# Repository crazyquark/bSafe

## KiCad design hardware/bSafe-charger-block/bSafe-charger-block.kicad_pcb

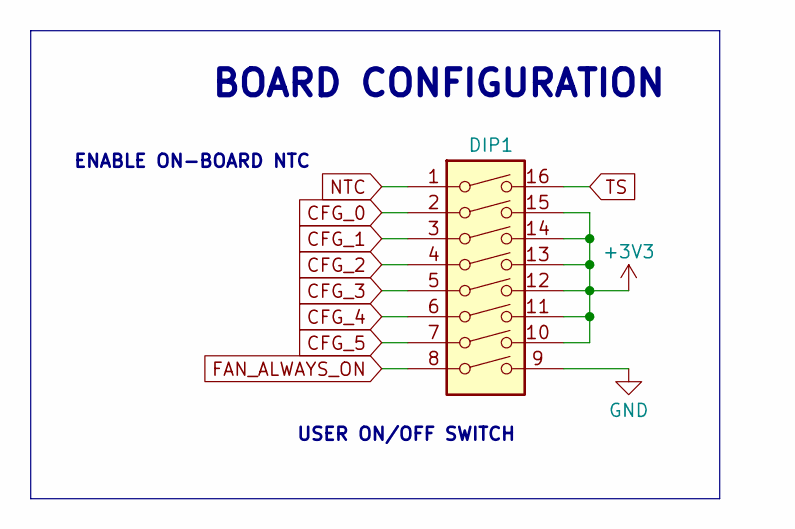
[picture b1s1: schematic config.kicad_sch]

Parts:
DIP1: SW_DIP_x08; SW_DIP_SPSTx08_Slide_Copal_CHS-08A_W5.08mm_P1.27mm_JPin

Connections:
+3V3: DIP1.10, DIP1.11, DIP1.12, DIP1.13, DIP1.14, DIP1.15; also elsewhere on the board
CFG_0: DIP1.2; also elsewhere on the board
CFG_1: DIP1.3; also elsewhere on the board
CFG_2: DIP1.4; also elsewhere on the board
CFG_3: DIP1.5; also elsewhere on the board
CFG_4: DIP1.6; also elsewhere on the board
CFG_5: DIP1.7; also elsewhere on the board
FAN_ALWAYS_ON: DIP1.8; also elsewhere on the board
GND: DIP1.9; also elsewhere on the board
NTC: DIP1.1; also elsewhere on the board
TS: DIP1.16; also elsewhere on the board

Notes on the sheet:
USER ON/OFF SWITCH
ENABLE ON-BOARD NTC
BOARD CONFIGURATION

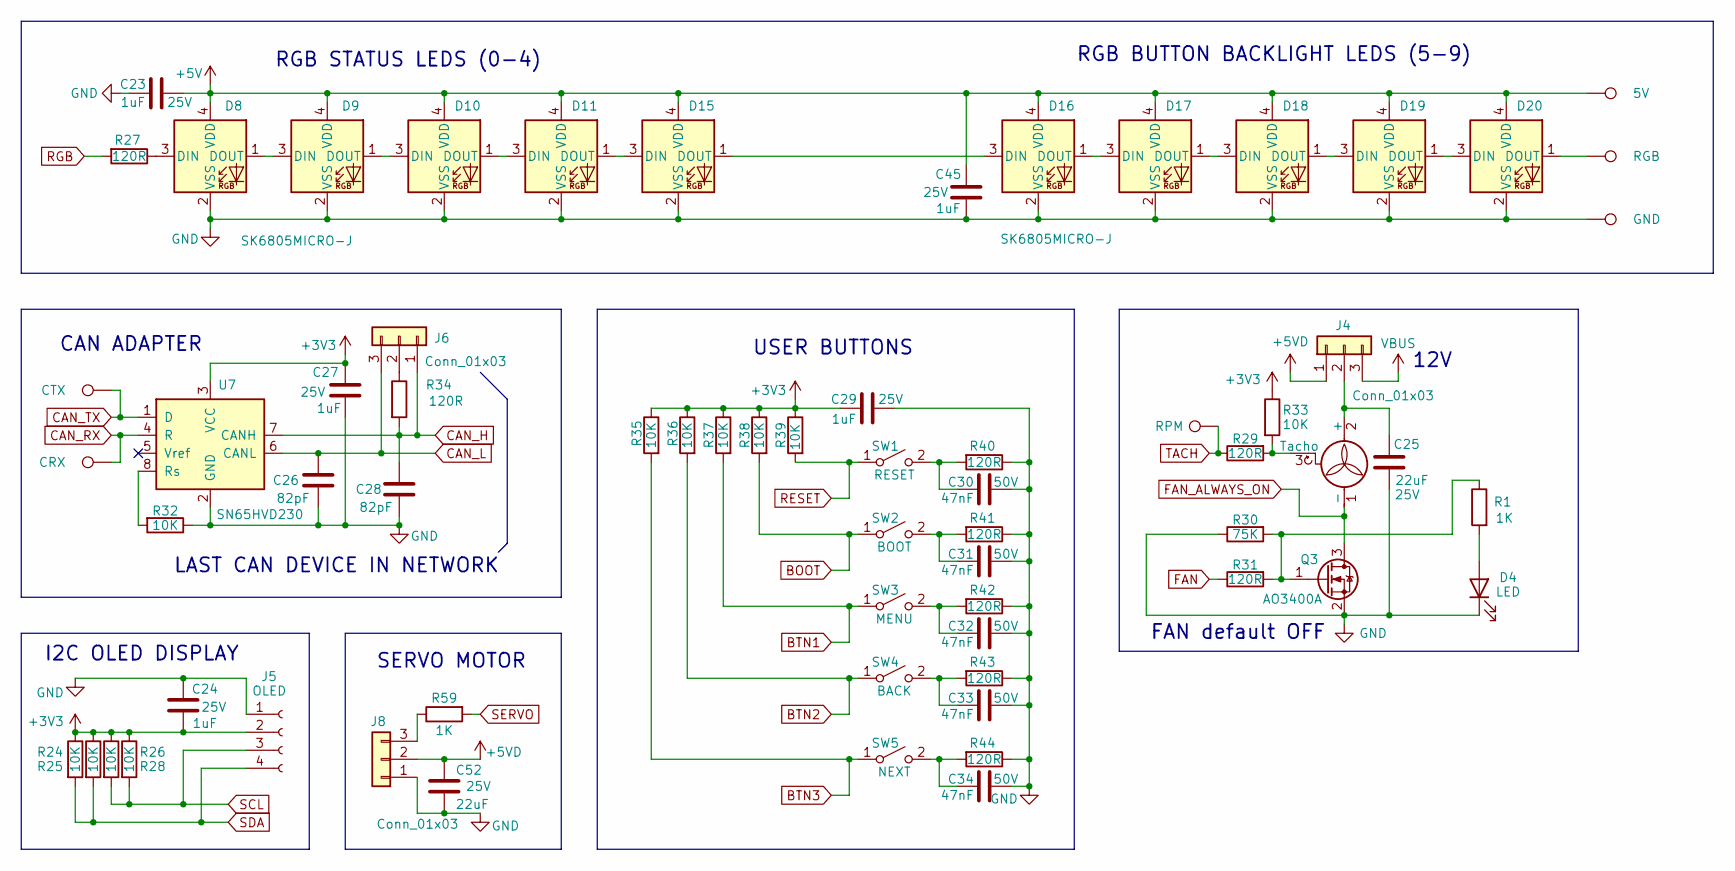
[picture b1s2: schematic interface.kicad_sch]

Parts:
C23, C24, C27, C29, C45: 1uF; C_0603_1608Metric; Voltage 25V
C25, C52: 22uF; C_0805_2012Metric; Voltage 25V
C26, C28: 82pF; C_0402_1005Metric
C30, C31, C32, C33, C34: 47nF; C_0402_1005Metric; Voltage 50V
D4: LED; LED_0402_1005Metric
D8, D9, D10, D11, D15, D16, D17, D18, D19, D20: SK6805MICRO-J; LED_SK6805_PLCC4_2.4x2.7mm_P1.3mm
J4, J6, J8: Conn_01x03; PinHeader_1x03_P2.54mm_Vertical
J5: OLED; Display_128x64_096_I2C
M1: Fan_3pin; Molex_KK-254_AE-6410-03A_1x03_P2.54mm_Vertical
Q3: AO3400A; SOT-23; JLCPCB C20917
R1, R59: 1K; R_0402_1005Metric
R24, R25, R26, R28, R32, R33, R35, R36, R37, R38, R39: 10K; R_0402_1005Metric
R27, R29, R31, R34, R40, R41, R42, R43, R44: 120R; R_0402_1005Metric
R30: 75K; R_0402_1005Metric
SW1: RESET; TS665WS
SW2: BOOT; TS665WS
SW3: MENU; TS665WS
SW4: BACK; TS665WS
SW5: NEXT; TS665WS
TP20: CTX; TestPoint_Pad_D1.5mm
TP21: CRX; TestPoint_Pad_D1.5mm
TP22: RPM; TestPoint_Pad_D1.5mm
TP25: 5V; TestPoint_Pad_D1.5mm
TP26: RGB; TestPoint_Pad_D1.5mm
TP27: GND; TestPoint_Pad_D1.5mm
U7: SN65HVD230; SOIC-8_3.9x4.9mm_P1.27mm

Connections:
+3V3: C24.2, C27.1, C29.2, J5.2, R24.1, R25.1, R26.1, R28.1, R33.1, R35.1, R36.1, R37.1, R38.1, R39.1, U7.3 (VCC); also elsewhere on the board
+5V: C23.1, C45.1, D8.4 (VDD), D9.4 (VDD), D10.4 (VDD), D11.4 (VDD), D15.4 (VDD), D16.4 (VDD), D17.4 (VDD), D18.4 (VDD), D19.4 (VDD), D20.4 (VDD), TP25.1; also elsewhere on the board
+5VD: C52.2, J4.1, J8.2; also elsewhere on the board
BOOT: R38.2, SW2.1 (A); also elsewhere on the board
BTN1: R37.2, SW3.1 (A); also elsewhere on the board
BTN2: R36.2, SW4.1 (A); also elsewhere on the board
BTN3: R35.2, SW5.1 (A); also elsewhere on the board
CAN_H: C28.1, J6.1, R34.2, U7.7 (CANH); also elsewhere on the board
CAN_L: C26.1, J6.3, U7.6 (CANL); also elsewhere on the board
CAN_RX: TP21.1, U7.4 (R); also elsewhere on the board
CAN_TX: TP20.1, U7.1 (D); also elsewhere on the board
FAN: R31.1; also elsewhere on the board
FAN_ALWAYS_ON: M1.1 (-), Q3.3 (D); also elsewhere on the board
GND: C23.2, C24.1, C25.2, C26.2, C27.2, C28.2, C29.1, C30.1, C31.1, C32.1, C33.1, C34.1, C45.2, C52.1, D4.1 (K), D8.2 (VSS), D9.2 (VSS), D10.2 (VSS), D11.2 (VSS), D15.2 (VSS), D16.2 (VSS), D17.2 (VSS), D18.2 (VSS), D19.2 (VSS), D20.2 (VSS), J5.1, J8.1, Q3.2 (S), R30.1, R32.1, R40.1, R41.1, R42.1, R43.1, R44.1, TP27.1, U7.2 (GND); also elsewhere on the board
unnamed: D4.2 (A), R1.2
unnamed: D8.3 (DIN), R27.1
unnamed: D8.1 (DOUT), D9.3 (DIN)
unnamed: D9.1 (DOUT), D10.3 (DIN)
unnamed: D10.1 (DOUT), D11.3 (DIN)
unnamed: D11.1 (DOUT), D15.3 (DIN)
unnamed: D15.1 (DOUT), D16.3 (DIN)
unnamed: D16.1 (DOUT), D17.3 (DIN)
unnamed: D17.1 (DOUT), D18.3 (DIN)
unnamed: D18.1 (DOUT), D19.3 (DIN)
unnamed: D19.1 (DOUT), D20.3 (DIN)
unnamed: D20.1 (DOUT), TP26.1
unnamed: C25.1, J4.2, M1.2 (+)
unnamed: J6.2, R34.1
unnamed: J8.3, R59.1
unnamed: M1.3 (Tacho), R29.2, R33.2
unnamed: Q3.1 (G), R1.1, R30.2, R31.2
unnamed: C30.2, R40.2, SW1.2 (B)
unnamed: C31.2, R41.2, SW2.2 (B)
unnamed: C32.2, R42.2, SW3.2 (B)
unnamed: C33.2, R43.2, SW4.2 (B)
unnamed: C34.2, R44.2, SW5.2 (B)
unnamed: R32.2, U7.8 (Rs)
RESET: R39.2, SW1.1 (A); also elsewhere on the board
RGB: R27.2; also elsewhere on the board
SCL: J5.3, R26.2, R28.2; also elsewhere on the board
SDA: J5.4, R24.2, R25.2; also elsewhere on the board
SERVO: R59.2; also elsewhere on the board
TACH: R29.1, TP22.1; also elsewhere on the board
VBUS: J4.3; also elsewhere on the board

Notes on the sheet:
I2C OLED DISPLAY
CAN ADAPTER
RGB STATUS LEDS (0-4)
SERVO MOTOR
RGB BUTTON BACKLIGHT LEDS (5-9)
FAN default OFF
12V
LAST CAN DEVICE IN NETWORK
USER BUTTONS

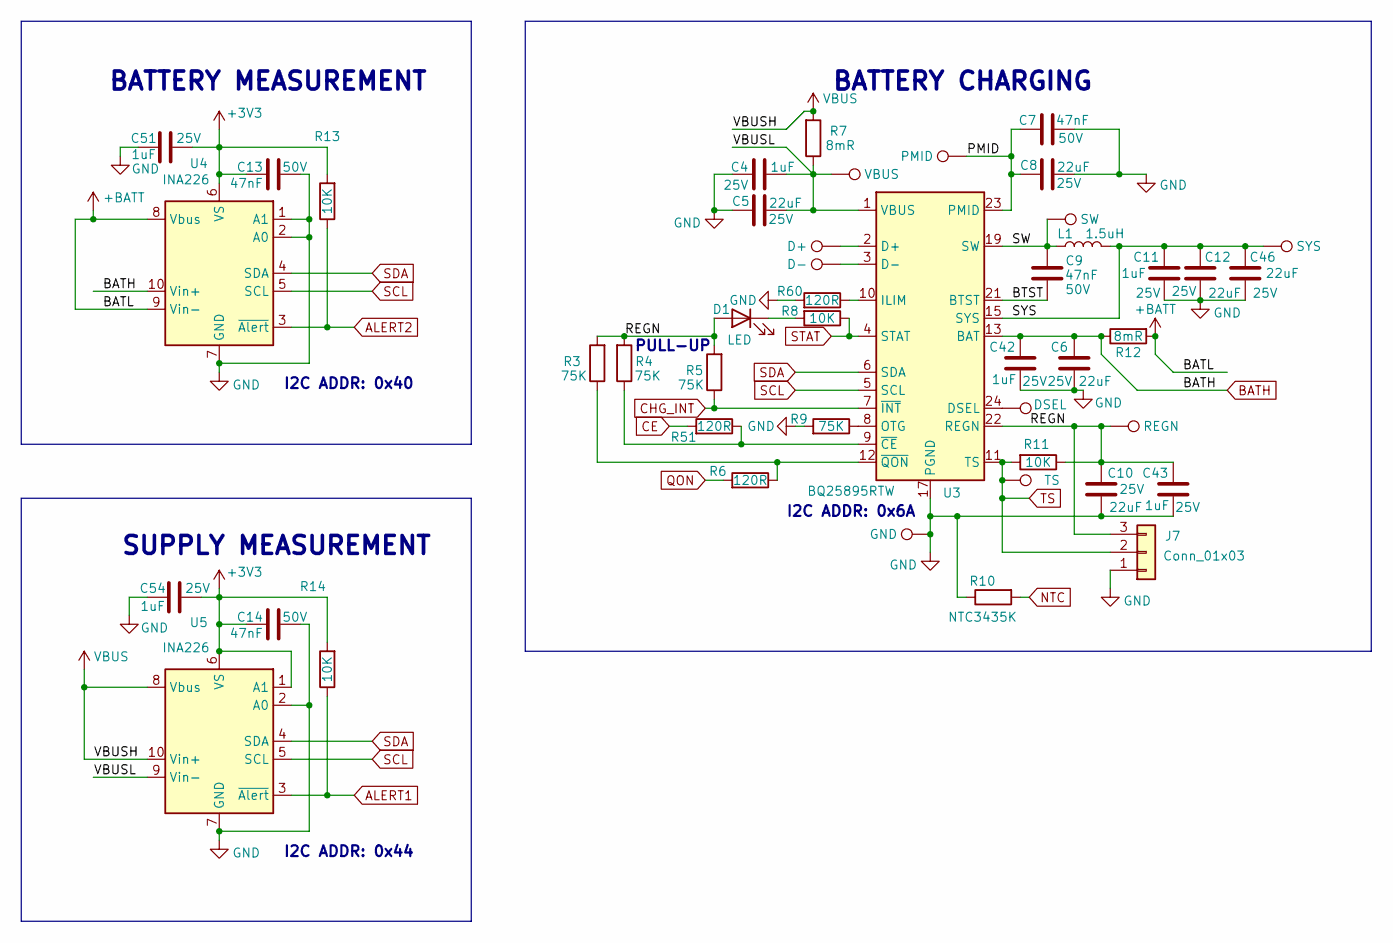
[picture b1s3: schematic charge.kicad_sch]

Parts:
C4, C11, C42, C43, C51, C54: 1uF; C_0603_1608Metric; Voltage 25V
C5, C6, C8, C10, C12, C46: 22uF; C_0805_2012Metric; Voltage 25V
C7, C9, C13, C14: 47nF; C_0402_1005Metric; Voltage 50V
D1: LED; LED_0402_1005Metric
J7: Conn_01x03; PinHeader_1x03_P2.54mm_Vertical
L1: 1.5uH; L_Sumida_CDMC6D28_7.25x6.5mm; JLCPCB C5189745
R3, R4, R5, R9: 75K; R_0402_1005Metric
R6, R51, R60: 120R; R_0402_1005Metric
R7, R12: 8mR; R_2512_6332Metric_Pad1.40x3.35mm_HandSolder
R8, R11, R13, R14: 10K; R_0402_1005Metric
R10: NTC3435K; R_0805_2012Metric_Pad1.20x1.40mm_HandSolder
TP3: DSEL; TestPoint_Pad_D1.5mm
TP4: SW; TestPoint_Pad_D1.5mm
TP7: VBUS; TestPoint_Pad_D1.5mm
TP9: PMID; TestPoint_Pad_D1.5mm
TP10: TS; TestPoint_Pad_D1.5mm
TP11: REGN; TestPoint_Pad_D1.5mm
TP13: SYS; TestPoint_Pad_D1.5mm
TP23: GND; TestPoint_Pad_D1.5mm
TP24: D+; TestPoint_Pad_D1.5mm
TP28: D-; TestPoint_Pad_D1.5mm
U3: BQ25895RTW; Texas_RTW_WQFN-24-1EP_4x4mm_P0.5mm_EP2.7x2.7mm_ThermalVias
U4, U5: INA226; VSSOP-10_3x3mm_P0.5mm

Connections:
+3V3: C13.2, C14.2, C51.1, C54.1, R13.2, R14.2, U4.6 (VS), U5.1 (A1), U5.6 (VS); also elsewhere on the board
+BATT: R12.2, U4.8 (Vbus), U4.9 (Vin-)
/charge/BTST: C9.1, U3.21 (BTST)
/charge/PMID: C7.2, C8.1, TP9.1, U3.23 (PMID)
/charge/REGN: C10.2, C43.2, D1.2 (A), J7.3, R3.2, R4.2, R5.2, R11.1, TP11.1, U3.22 (REGN)
/charge/SW: C9.2, L1.1, TP4.1, U3.19 (SW), U3.20 (SW)
/charge/SYS: C11.2, C12.1, C46.1, L1.2, TP13.1, U3.15 (SYS), U3.16 (SYS)
/charge/VBUSL: C4.1, C5.2, R7.1, TP7.1, U3.1 (VBUS), U5.9 (Vin-)
ALERT1: R14.1, U5.3 (~Alert); also elsewhere on the board
ALERT2: R13.1, U4.3 (~Alert); also elsewhere on the board
BATH: C6.1, C42.2, R12.1, U3.13 (BAT), U3.14 (BAT), U4.10 (Vin+); also elsewhere on the board
CE: R51.2; also elsewhere on the board
CHG_INT: R5.1, U3.7 (~INT); also elsewhere on the board
GND: C4.2, C5.1, C6.2, C7.1, C8.2, C10.1, C11.1, C12.2, C13.1, C14.1, C42.1, C43.1, C46.2, C51.2, C54.2, J7.1, R9.2, R10.1, R60.2, TP23.1, U3.17 (PGND), U3.18 (PGND), U3.25 (PGND), U4.1 (A1), U4.2 (A0), U4.7 (GND), U5.2 (A0), U5.7 (GND); also elsewhere on the board
NTC: R10.2; also elsewhere on the board
unnamed: D1.1 (K), R8.2
unnamed: TP24.1, U3.2 (D+)
unnamed: TP28.1, U3.3 (D-)
unnamed: TP3.1, U3.24 (DSEL)
unnamed: R60.1, U3.10 (ILIM)
unnamed: R9.1, U3.8 (OTG)
unnamed: R4.1, R51.1, U3.9 (~CE)
unnamed: R3.1, R6.1, U3.12 (~QON)
QON: R6.2; also elsewhere on the board
SCL: U3.5 (SCL), U4.5 (SCL), U5.5 (SCL); also elsewhere on the board
SDA: U3.6 (SDA), U4.4 (SDA), U5.4 (SDA); also elsewhere on the board
STAT: R8.1, U3.4 (STAT); also elsewhere on the board
TS: J7.2, R11.2, TP10.1, U3.11 (TS); also elsewhere on the board
VBUS: R7.2, U5.8 (Vbus), U5.10 (Vin+); also elsewhere on the board

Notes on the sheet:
SUPPLY MEASUREMENT
I2C ADDR: 0x44
I2C ADDR: 0x40
BATTERY CHARGING
I2C ADDR: 0x6A
PULL-UP
BATTERY MEASUREMENT

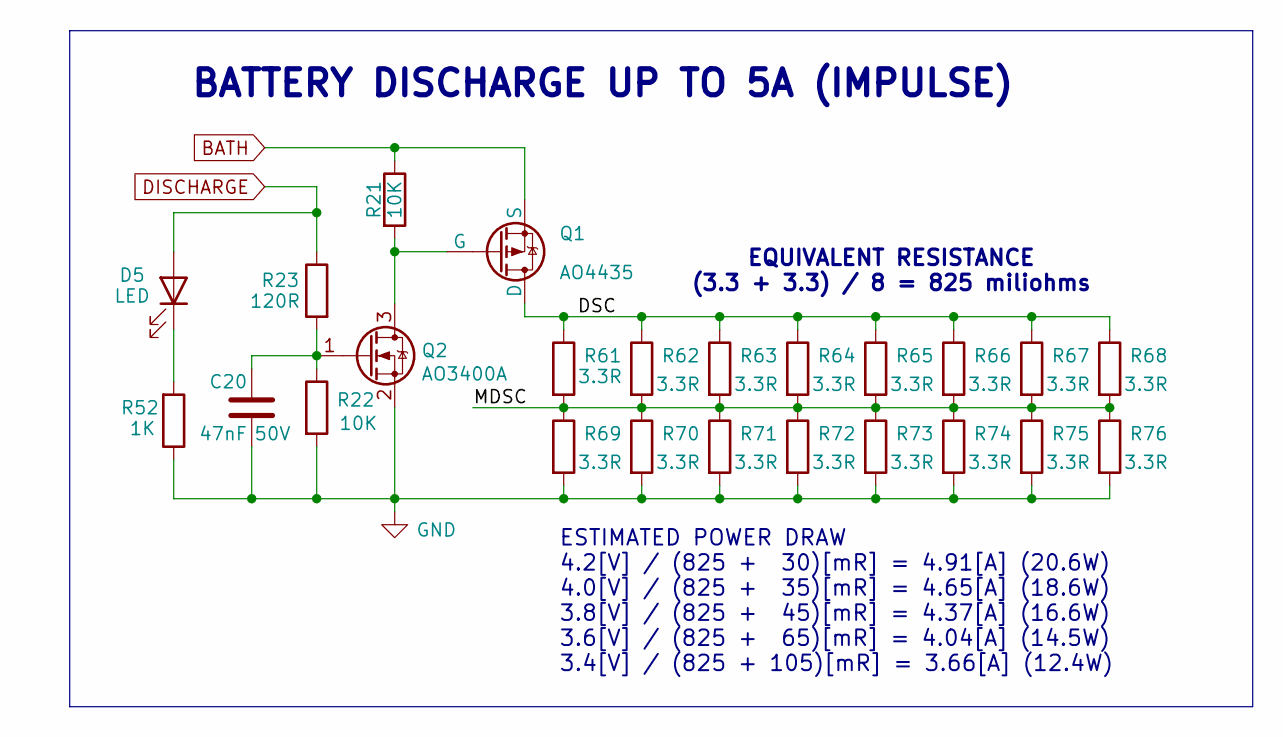
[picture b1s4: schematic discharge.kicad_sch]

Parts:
C20: 47nF; C_0402_1005Metric; Voltage 50V
D5: LED; LED_0402_1005Metric
Q1: AO4435; SOP-8_3.76x4.96mm_P1.27mm
Q2: AO3400A; SOT-23; JLCPCB C20917
R21, R22: 10K; R_0402_1005Metric
R23: 120R; R_0402_1005Metric
R52: 1K; R_0402_1005Metric
R61, R62, R63, R64, R65, R66, R67, R68, R69, R70, R71, R72, R73, R74, R75, R76: 3.3R; R_2512_6332Metric_Pad1.40x3.35mm_HandSolder

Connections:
/discharge/DSC: Q1.5 (D), Q1.6 (D), Q1.7 (D), Q1.8 (D), R61.1, R62.1, R63.1, R64.1, R65.1, R66.1, R67.1, R68.1
/discharge/MDSC: R61.2, R62.2, R63.2, R64.2, R65.2, R66.2, R67.2, R68.2, R69.1, R70.1, R71.1, R72.1, R73.1, R74.1, R75.1, R76.1
BATH: Q1.1 (S), Q1.2 (S), Q1.3 (S), R21.1; also elsewhere on the board
DISCHARGE: D5.2 (A), R23.1; also elsewhere on the board
GND: C20.2, Q2.2 (S), R22.2, R52.1, R69.2, R70.2, R71.2, R72.2, R73.2, R74.2, R75.2, R76.2; also elsewhere on the board
unnamed: D5.1 (K), R52.2
unnamed: Q1.4 (G), Q2.3 (D), R21.2
unnamed: C20.1, Q2.1 (G), R22.1, R23.2

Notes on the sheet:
EQUIVALENT RESISTANCE (3.3 + 3.3) / 8 = 825 miliohms
ESTIMATED POWER DRAW 4.2[V] / (825 + 30)[mR] = 4.91[A] (20.6W) 4.0[V] / (825 + 35)[mR] = 4.65[A] (18.6W) 3.8[V] / (825 + 45)[mR] = 4.37[A] (16.6W) 3.6[V] / (825 + 65)[mR] = 4.04[A] (14.5W) 3.4[V] / (825 + 105)[mR] = 3.66[A] (12.4W)
BATTERY DISCHARGE UP TO 5A (IMPULSE)

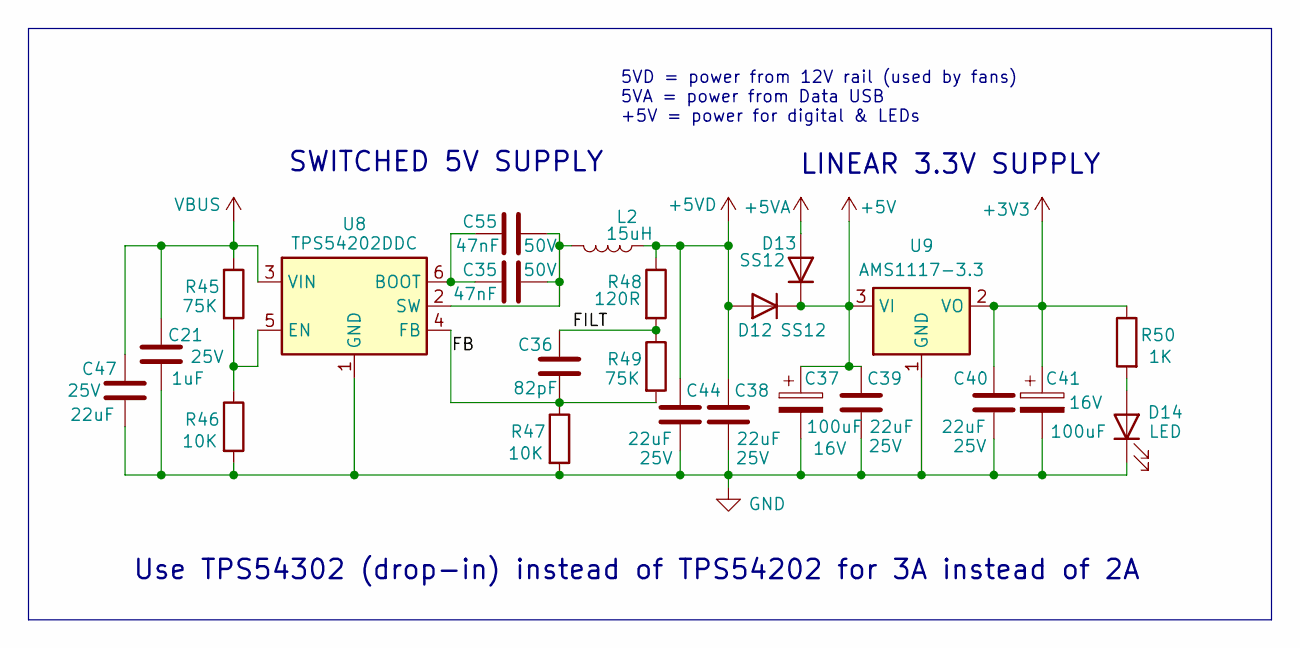
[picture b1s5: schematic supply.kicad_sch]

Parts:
C21: 1uF; C_0603_1608Metric; Voltage 25V
C35, C55: 47nF; C_0402_1005Metric; Voltage 50V
C36: 82pF; C_0402_1005Metric
C37, C41: 100uF; CP_Elec_6.3x5.4_Nichicon; Voltage 16V
C38, C39, C40, C44, C47: 22uF; C_0805_2012Metric; Voltage 25V
D12, D13: SS12; D_SMA
D14: LED; LED_0402_1005Metric
L2: 15uH; L_Taiyo-Yuden_NR-60xx
R45, R49: 75K; R_0402_1005Metric
R46, R47: 10K; R_0402_1005Metric
R48: 120R; R_0402_1005Metric
R50: 1K; R_0402_1005Metric
U8: TPS54202DDC; SOT-23-6
U9: AMS1117-3.3; SOT-223-3_TabPin2

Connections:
+3V3: C40.1, C41.1, R50.1, U9.2 (VO); also elsewhere on the board
+5V: C37.1, C39.1, D12.1 (K), D13.1 (K), U9.3 (VI); also elsewhere on the board
+5VA: D13.2 (A); also elsewhere on the board
+5VD: C38.1, C44.1, D12.2 (A), L2.2, R48.1; also elsewhere on the board
/supply/FB: C36.2, R47.1, R49.2, U8.4 (FB)
/supply/FILT: C36.1, R48.2, R49.1
GND: C21.2, C37.2, C38.2, C39.2, C40.2, C41.2, C44.2, C47.1, D14.1 (K), R46.2, R47.2, U8.1 (GND), U9.1 (GND); also elsewhere on the board
unnamed: D14.2 (A), R50.2
unnamed: C35.2, C55.2, U8.6 (BOOT)
unnamed: R45.2, R46.1, U8.5 (EN)
unnamed: C35.1, C55.1, L2.1, U8.2 (SW)
VBUS: C21.1, C47.2, R45.1, U8.3 (VIN); also elsewhere on the board

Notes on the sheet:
5VD = power from 12V rail (used by fans) 5VA = power from Data USB +5V = power for digital & LEDs
SWITCHED 5V SUPPLY
Use TPS54302 (drop-in) instead of TPS54202 for 3A instead of 2A
LINEAR 3.3V SUPPLY

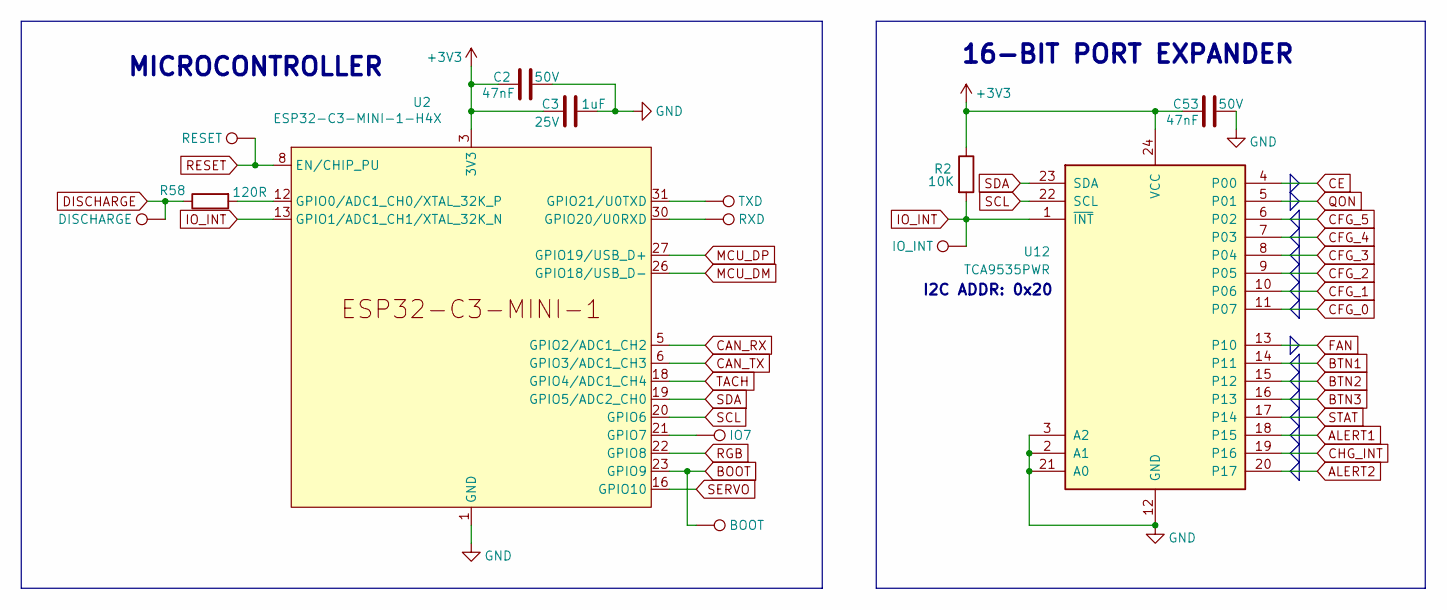
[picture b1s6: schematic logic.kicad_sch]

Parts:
C2, C53: 47nF; C_0402_1005Metric; Voltage 50V
C3: 1uF; C_0603_1608Metric; Voltage 25V
R2: 10K; R_0402_1005Metric
R58: 120R; R_0402_1005Metric
TP1: IO_INT; TestPoint_Pad_D1.5mm
TP2: IO7; TestPoint_Pad_D1.5mm
TP5: TXD; TestPoint_Pad_D1.5mm
TP6: RXD; TestPoint_Pad_D1.5mm
TP8: DISCHARGE; TestPoint_Pad_D1.5mm
TP30: RESET; TestPoint_Pad_D1.5mm
TP31: BOOT; TestPoint_Pad_D1.5mm
U2: ESP32-C3-MINI-1-H4X; ESP32-C3-MINI-1
U12: TCA9535PWR; TSSOP-24_4.4x7.8mm_P0.65mm

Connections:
+3V3: C2.2, C3.2, C53.2, R2.1, U2.3 (3V3), U12.24 (VCC); also elsewhere on the board
ALERT1: U12.18 (P15); also elsewhere on the board
ALERT2: U12.20 (P17); also elsewhere on the board
BOOT: TP31.1, U2.23 (GPIO9); also elsewhere on the board
BTN1: U12.14 (P11); also elsewhere on the board
BTN2: U12.15 (P12); also elsewhere on the board
BTN3: U12.16 (P13); also elsewhere on the board
CAN_RX: U2.5 (GPIO2/ADC1_CH2); also elsewhere on the board
CAN_TX: U2.6 (GPIO3/ADC1_CH3); also elsewhere on the board
CE: U12.4 (P00); also elsewhere on the board
CFG_0: U12.11 (P07); also elsewhere on the board
CFG_1: U12.10 (P06); also elsewhere on the board
CFG_2: U12.9 (P05); also elsewhere on the board
CFG_3: U12.8 (P04); also elsewhere on the board
CFG_4: U12.7 (P03); also elsewhere on the board
CFG_5: U12.6 (P02); also elsewhere on the board
CHG_INT: U12.19 (P16); also elsewhere on the board
DISCHARGE: R58.1, TP8.1; also elsewhere on the board
FAN: U12.13 (P10); also elsewhere on the board
GND: C2.1, C3.1, C53.1, U2.1 (GND), U2.2 (GND), U2.11 (GND), U2.14 (GND), U2.36 (GND), U2.37 (GND), U2.38 (GND), U2.39 (GND), U2.40 (GND), U2.41 (GND), U2.42 (GND), U2.43 (GND), U2.44 (GND), U2.45 (GND), U2.46 (GND), U2.47 (GND), U2.48 (GND), U2.49 (GND), U2.50 (GND), U2.51 (GND), U2.52 (GND), U2.53 (GND), U12.2 (A1), U12.3 (A2), U12.12 (GND), U12.21 (A0); also elsewhere on the board
IO_INT: R2.2, TP1.1, U2.13 (GPIO1/ADC1_CH1/XTAL_32K_N), U12.1 (~INT)
MCU_DM: U2.26 (GPIO18/USB_D-); also elsewhere on the board
MCU_DP: U2.27 (GPIO19/USB_D+); also elsewhere on the board
unnamed: R58.2, U2.12 (GPIO0/ADC1_CH0/XTAL_32K_P)
unnamed: TP2.1, U2.21 (GPIO7)
unnamed: TP6.1, U2.30 (GPIO20/U0RXD)
unnamed: TP5.1, U2.31 (GPIO21/U0TXD)
QON: U12.5 (P01); also elsewhere on the board
RESET: TP30.1, U2.8 (EN/CHIP_PU); also elsewhere on the board
RGB: U2.22 (GPIO8); also elsewhere on the board
SCL: U2.20 (GPIO6), U12.22 (SCL); also elsewhere on the board
SDA: U2.19 (GPIO5/ADC2_CH0), U12.23 (SDA); also elsewhere on the board
SERVO: U2.16 (GPIO10); also elsewhere on the board
STAT: U12.17 (P14); also elsewhere on the board
TACH: U2.18 (GPIO4/ADC1_CH4); also elsewhere on the board

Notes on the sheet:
MICROCONTROLLER
16-BIT PORT EXPANDER
I2C ADDR: 0x20

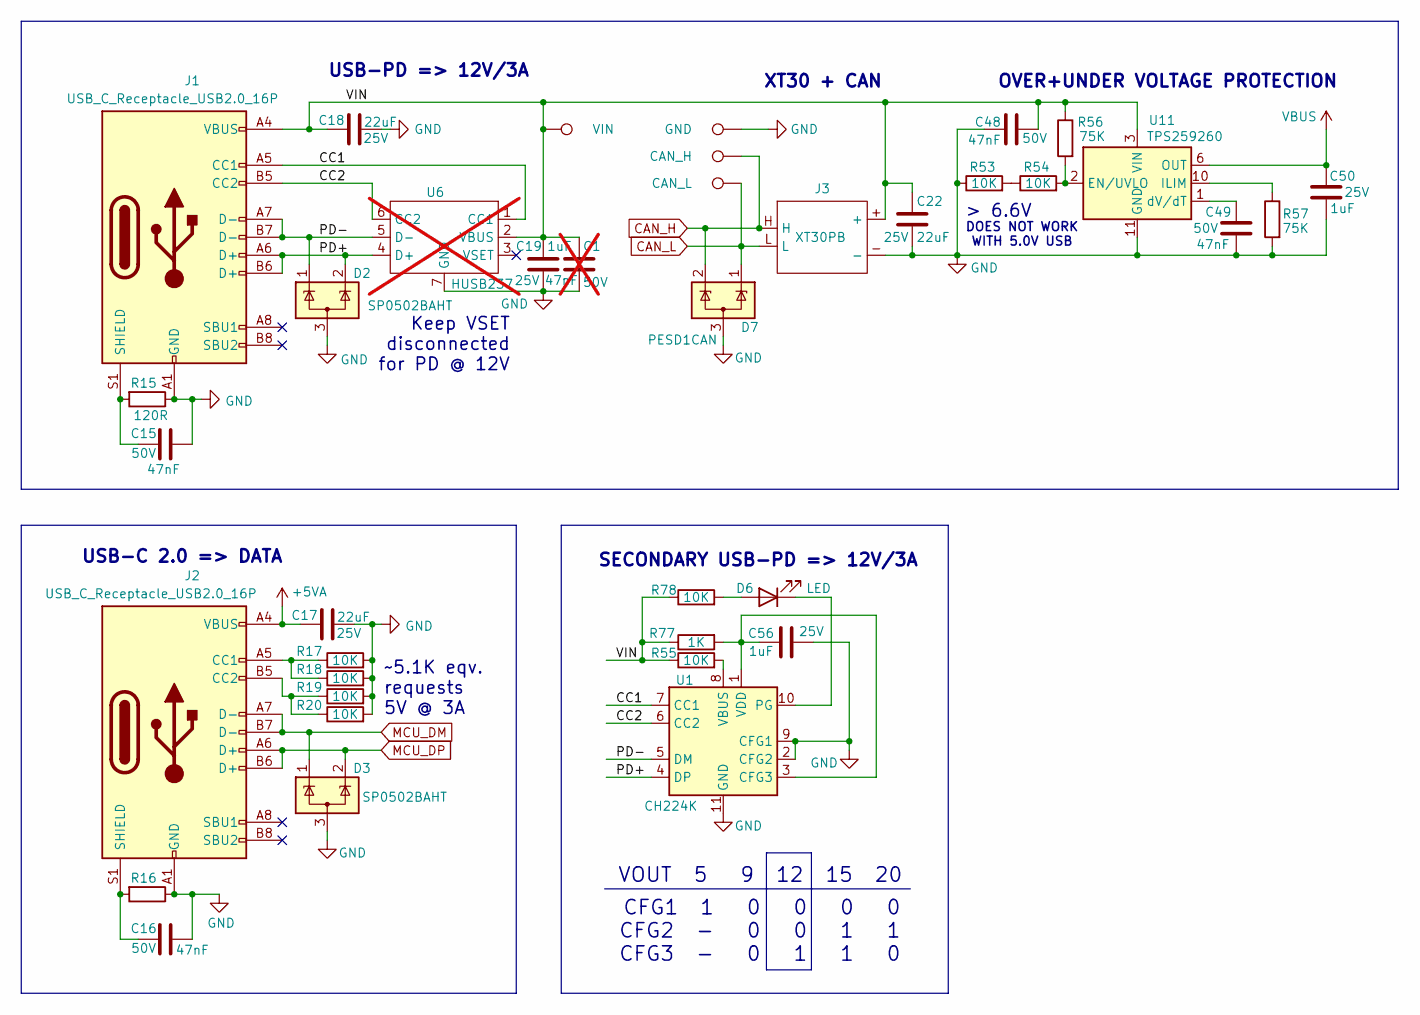
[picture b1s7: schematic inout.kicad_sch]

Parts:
C1: 47nF; C_0402_1005Metric; Voltage 50V; not fitted
C15, C16, C48, C49: 47nF; C_0402_1005Metric; Voltage 50V
C17, C18, C22: 22uF; C_0805_2012Metric; Voltage 25V
C19, C50, C56: 1uF; C_0603_1608Metric; Voltage 25V
D2, D3: SP0502BAHT; SOT-23
D6: LED; LED_0402_1005Metric
D7: PESD1CAN; SOT-23-3
J1, J2: USB_C_Receptacle_USB2.0_16P; USB_C_Receptacle_G-Switch_GT-USB-7010ASV
J3: XT30PB
R15, R16: 120R; R_0402_1005Metric
R17, R18, R19, R20, R53, R54, R55, R78: 10K; R_0402_1005Metric
R56, R57: 75K; R_0402_1005Metric
R77: 1K; R_0402_1005Metric
TP16: VIN; TestPoint_Pad_D1.5mm
TP17: GND; TestPoint_Pad_D1.5mm
TP18: CAN_H; TestPoint_Pad_D1.5mm
TP19: CAN_L; TestPoint_Pad_D1.5mm
U1: CH224K; SSOP-10-1EP_3.9x4.9mm_P1mm_EP2.1x3.3mm
U6: HUSB237; DFN-6-1EP_2x2mm_P0.65mm_EP1.01x1.7mm; not fitted
U11: TPS259260; VSON-10-1EP_3x3mm_P0.5mm_EP1.65x2.4mm_ThermalVias

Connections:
+5VA: C17.1, J2.A4 (VBUS), J2.A9 (VBUS), J2.B4 (VBUS), J2.B9 (VBUS); also elsewhere on the board
/input/CC1: J1.A5 (CC1), U1.7 (CC1), U6.1 (CC1)
/input/CC2: J1.B5 (CC2), U1.6 (CC2), U6.6 (CC2)
/input/PD+: D2.2 (K), J1.A6 (D+), J1.B6 (D+), U1.4 (DP), U6.4 (D+)
/input/PD-: D2.1 (K), J1.A7 (D-), J1.B7 (D-), U1.5 (DM), U6.5 (D-)
/input/VIN: C1.1, C18.1, C19.1, C22.2, C48.2, J1.A4 (VBUS), J1.A9 (VBUS), J1.B4 (VBUS), J1.B9 (VBUS), J3.+, R55.1, R56.1, R77.1, R78.1, TP16.1, U6.2 (VBUS), U11.3 (VIN), U11.4 (VIN), U11.5 (VIN)
CAN_H: D7.2 (K), J3.H, TP18.1; also elsewhere on the board
CAN_L: D7.1 (K), J3.L, TP19.1; also elsewhere on the board
GND: C1.2, C15.2, C16.2, C17.2, C18.2, C19.2, C22.1, C48.1, C49.1, C50.1, C56.1, D2.3 (A), D3.3 (A), D7.3 (A), J1.A1 (GND), J1.A12 (GND), J1.B1 (GND), J1.B12 (GND), J2.A1 (GND), J2.A12 (GND), J2.B1 (GND), J2.B12 (GND), J3.-, R15.1, R16.1, R17.2, R18.2, R19.2, R20.2, R53.1, R57.2, TP17.1, U1.2 (CFG2), U1.9 (CFG1), U1.11 (GND), U6.7 (GND), U11.11 (GND); also elsewhere on the board
MCU_DM: D3.1 (K), J2.A7 (D-), J2.B7 (D-); also elsewhere on the board
MCU_DP: D3.2 (K), J2.A6 (D+), J2.B6 (D+); also elsewhere on the board
unnamed: D6.2 (A), R78.2
unnamed: D6.1 (K), U1.10 (PG)
unnamed: C15.1, J1.S1 (SHIELD), R15.2
unnamed: J2.A5 (CC1), R17.1, R18.1
unnamed: J2.B5 (CC2), R19.1, R20.1
unnamed: C16.1, J2.S1 (SHIELD), R16.2
unnamed: R53.2, R54.1
unnamed: C56.2, R77.2, U1.1 (VDD), U1.3 (CFG3)
unnamed: R55.2, U1.8 (VBUS)
unnamed: R54.2, R56.2, U11.2 (EN/UVLO)
unnamed: R57.1, U11.10 (ILIM)
unnamed: C49.2, U11.1 (dV/dT)
VBUS: C50.2, U11.6 (OUT), U11.7 (OUT), U11.8 (OUT); also elsewhere on the board

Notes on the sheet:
VOUT 5 9 12 15 20
SECONDARY USB-PD => 12V/3A
DOES NOT WORK WITH 5.0V USB
USB-PD => 12V/3A
XT30 + CAN
> 6.6V
CFG1 1 0 0 0 0 CFG2 - 0 0 1 1 CFG3 - 0 1 1 0
USB-C 2.0 => DATA
~5.1K eqv. requests 5V @ 3A
Keep VSET disconnected for PD @ 12V
OVER+UNDER VOLTAGE PROTECTION

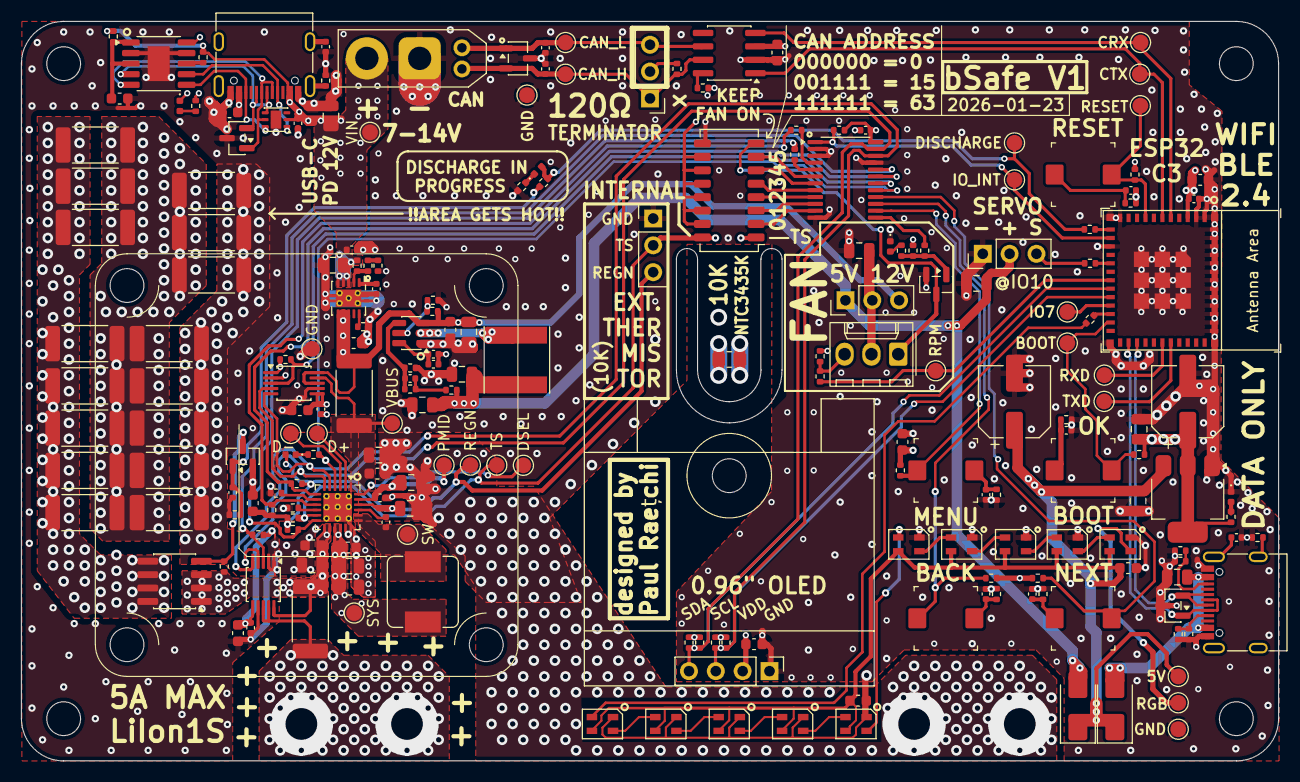
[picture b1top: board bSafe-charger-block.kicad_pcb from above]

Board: 4 copper layers, 119.0 x 70.0 mm, 212 parts (0 on the bottom side), 111 nets.

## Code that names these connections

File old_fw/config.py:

# config.py
# DO NOT MODIFY AT RUNTIME

from micropython import const

# ------------------------
# I2C
# ------------------------
I2C_SDA = const(5)
I2C_SCL = const(6)
I2C_FREQ = const(400_000)

INA226_ADDR_BATT = const(0x40)
INA226_ADDR_SYS  = const(0x44)
BQ25895_ADDR     = const(0x6A)
TCA9535_ADDR     = const(0x20)
OLED_ADDR        = const(0x3C)

# ------------------------
# Shunt & resistance
# ------------------------
SHUNT_RESISTANCE_OHMS = 0.008       # 8 milliohms
CIRCUIT_R_CHARGE_MOHM = 25
CIRCUIT_R_DISCHG_MOHM = 25
DISCHARGE_RESISTOR_OHMS = 0.85

# --- TCA9535 directions (1=input, 0=output)
# Port 0: CE(0), QON(1) outputs; CFG_0..CFG_5 inputs
TCA_DIR0 = const(0b11111100)

# Port 1: FAN (pin 8 -> port1 bit0) output; all others inputs
TCA_DIR1 = const(0b11111110)

# --- INA226 defaults (placeholders; tuned later)
# Precision-oriented defaults: moderate averaging + longer conv times
INA_AVG_SAMPLES = const(16)     # 1,4,16,64,128,256,512,1024
INA_VBUS_CT_US  = const(1100)   # 140,204,332,588,1100,2116,4156,8244
INA_VSH_CT_US   = const(1100)

# Alert defaults (we'll set at runtime based on chemistry/settings)
INA_ALERT_LATCHED = True
INA_ALERT_POLARITY_ACTIVE_LOW = True  # matches your pulled-up inputs

# ------------------------
# MCU GPIOs
# ------------------------
PIN_DISCHARGE = const(12)   # active-high
PIN_TACH      = const(18)
PIN_RGB       = const(22)
PIN_SERVO     = const(16)

PIN_CAN_RX    = const(5)
PIN_CAN_TX    = const(6)

PIN_IO_INT    = const(13)   # TCA9535 INT (active-low)

# ------------------------
# TCA9535 pin mapping
# ------------------------
# Port 0
P_CE       = const(0)
P_QON      = const(1)
P_CFG_5    = const(2)
P_CFG_4    = const(3)
P_CFG_3    = const(4)
P_CFG_2    = const(5)
P_CFG_1    = const(6)
P_CFG_0    = const(7)

# Port 1
P_FAN      = const(8)
P_BTN1     = const(9)
P_BTN2     = const(10)
P_BTN3     = const(11)
P_STAT     = const(12)
P_ALERT1   = const(13)
P_CHG_INT  = const(14)
P_ALERT2   = const(15)

# ------------------------
# UI Pages
# ------------------------
PAGE_STATUS = const(0)
PAGE_CONFIG = const(1)
PAGE_HEALTH = const(2)
PAGE_MODE   = const(3)

STATUS_ROTATE_MS = const(5000)

# ------------------------
# RGB colors (RGB tuples)
# ------------------------
RGB_PRECONDITION = (255,  20, 147)   # pink
RGB_CHARGE       = (160,  32, 240)   # purple
RGB_WAIT         = (255, 255,   0)   # yellow
RGB_DISCHARGE    = (255,   0,   0)   # red
RGB_RECHARGE     = (  0,   0, 255)   # blue
RGB_DONE         = (  0, 255,   0)   # green
RGB_IDLE         = (  0,   0,   0)

# ------------------------
# Chemistry definitions
# ------------------------
CHEMISTRIES = {
    "LTO":     2.40,
    "LFP":     3.60,
    "LCO":     4.20,
    "HV-LCO":  4.35,
    "LMNO":    4.10,
}

MAX_CELLS_PARALLEL = 16

# TS / NTC conversion (BQ25895 TS pin divider: REGN --10k-- TS -- NTC -- GND)
TS_PULLUP_OHMS = 10000
TS_NTC_R0_OHMS = 10000     # assumed 10k NTC @ 25C
TS_NTC_BETA_K = 3435
TS_NTC_T0_C = 25.0

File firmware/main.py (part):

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from machine import Pin, PWM, ADC
from board import Board

# External NTC divider constants
_EXT_R_PULL_OHM = 10_000.0     # 10k pull-up to 3V3
_EXT_R0_OHM     = 89_000.0     # ~100k NTC @ 25C
_EXT_BETA_K     = 3950.0       # adjust to your NTC (e.g. 3435, 3950, 4100...)
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
def read_ext_temp() -> float | None:
    """
    External NTC on GPIO1 via divider:
      3V3 -- 10k -- ADC(GPIO1) -- NTC -- GND
    Uses Steinhart-Hart fit to your measured points:
      35C@3.2V, 45C@3.0V, 77C@2.1V (assuming Vref=3.3 and Rpull=10k).
    """
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        self.board = Board()
        self.oled = None

        # OK (BOOT) is on MCU GPIO9
        self.pin_ok = Pin(9, Pin.IN, Pin.PULL_UP)

        # --- SK6812 setup (GPIO8) ---
        self._led_pin = Pin(8, Pin.OUT)
        self._leds = NeoPixel(self._led_pin, 10)  # total strip length = 10

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        self.P_QON = getattr(cfg, "P_QON", None)   # output, pulse high to wake BQ
        self.P_CE  = getattr(cfg, "P_CE", None)    # output, active-low enable

        # TACH is on MCU (GPIO4)
        self.pin_tach = Pin(4, Pin.IN, Pin.PULL_UP)
        self.TACH_PPR = 2

        # --- DISCHARGE/MEASURE load PWM (GPIO0), active high ---
        self._dsc_pwm = None
        self._dsc_pct = 10  # percent, min 10, max 100, step 5
        self._dsc_duty = int(1023 * self._dsc_pct / 100.0)
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        self._tach_timeout_us = 2_000_000  # 2s -> consider stopped

        try:
            self.pin_tach.irq(trigger=Pin.IRQ_FALLING, handler=self._tach_irq)
        except Exception:
            pass

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        # Ensure charger is disabled while discharging
        self._set_ce_enabled(False)

        # Start PWM on GPIO0 at current RATE (%)
        self._dsc_duty = int(1023 * self._dsc_pct / 100.0)
        try:
            if self._dsc_pwm is None:
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
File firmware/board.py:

from machine import Pin, I2C
import time

import config

# Real drivers (if present on I2C)
from drivers.tca9535 import TCA9535
from drivers.ina226 import INA226
from drivers.bq25895 import BQ25895

class Board:
    def __init__(self):
        self.i2c = None
        
        self.btn_ok = Pin(9, Pin.IN)  # GPIO9, active-low

        # Devices
        self.exp = None
        self.ina_batt = None
        self.ina_sys = None
        self.bq = None
        self.has_exp = False
        self.has_ina_batt = False
        self.has_ina_sys = False
        self.has_bq = False

        # Inputs
        self.pin_io_int = None

        # cached
        self.in0 = 0xFF
        self.in1 = 0xFF
        self._btn_prev = {"menu": False, "left": False, "right": False, "ok": False}

    def init_i2c(self):
        self.i2c = I2C(
            0,
            scl=Pin(config.I2C_SCL),
            sda=Pin(config.I2C_SDA),
            freq=config.I2C_FREQ,
        )
        return self.i2c

    def _scan(self):
        try:
            return set(self.i2c.scan())
        except Exception:
            return set()

    # -------------------------
    # Expander (optional)
    # -------------------------
    def init_expander(self):
        addrs = self._scan()
        if config.TCA9535_ADDR not in addrs:
            print("WARN: TCA9535 not found at 0x{:02X}".format(config.TCA9535_ADDR))
            self.exp = None
            self.has_exp = False
            # self.pin_io_int = Pin(1, Pin.IN)
            return False

        try:
            self.exp = TCA9535(self.i2c, config.TCA9535_ADDR)
            self.exp.configure(config.TCA_DIR0, config.TCA_DIR1)

            # Default safe output states:
            # /CE HIGH = disabled by default (active-low)
            self._set_pin(config.P_CE, 1)
            self._set_pin(config.P_QON, 0)
            self._set_pin(config.P_FAN, 0)

            self.in0, self.in1 = self.exp.read_all()
            self.has_exp = True
        except Exception as e:
            print("WARN: TCA9535 init failed.", e)
            self.exp = None
            self.has_exp = False
        # self.pin_io_int = Pin(1, Pin.IN)
        return self.has_exp

    def _set_pin(self, pin, value):
        if self.exp is None:
            return
        self.exp.write_pin(pin, 1 if value else 0)

    def int_asserted(self) -> bool:
        return self.pin_io_int is not None and self.pin_io_int.value() == 0
    
    def _refresh_exp_inputs(self):
        if self.exp is None:
            return
        try:
            self.in0, self.in1 = self.exp.read_all()
        except:
            # keep old values on read failure
            pass

    def _pin_is_low(self, pin) -> bool:
        """
        Reads cached expander inputs and returns True if that expander pin is LOW.
        This matches your hardware: 10K pull-ups, button pulls to GND when pressed.
        """
        # If your TCA9535 driver uses 0..15 pin numbering, this works:
        if pin < 8:
            return ((self.in0 >> pin) & 1) == 0
        else:
            b = pin - 8
            return ((self.in1 >> b) & 1) == 0

    def poll_button_edges(self):
        # If expander present, refresh its cached inputs (polling is simplest/reliable)
        if getattr(self, "has_exp", False) and self.exp is not None:
            self._refresh_exp_inputs()

            menu_pressed  = self._exp_pin_low(config.P_BTN1)  # BTN1 = MENU
            left_pressed  = self._exp_pin_low(config.P_BTN2)  # BTN2 = LEFT
            right_pressed = self._exp_pin_low(config.P_BTN3)  # BTN3 = RIGHT

        # OK is ALWAYS GPIO9 (BOOT), active-low
        ok_pressed = (self.btn_ok.value() == 0)

        pressed = {
            "menu": menu_pressed,
            "left": left_pressed,
            "right": right_pressed,
            "ok": ok_pressed,
        }

        # Edge detect: only emit press events
        edges = {}
        for k, v in pressed.items():
            prev = self._btn_prev.get(k, False)
            edges[k] = (v and not prev)
            self._btn_prev[k] = v

        return edges


    # -------------------------
    # INA226 (optional)
    # -------------------------
    def init_ina226(self, max_current_a=5.0):
        addrs = self._scan()

        if config.INA226_ADDR_BATT in addrs:
            try:
                self.ina_batt = INA226(self.i2c, config.INA226_ADDR_BATT, config.SHUNT_RESISTANCE_OHMS)
                self.ina_batt.reset()
                self.ina_batt.configure_precision(config.INA_AVG_SAMPLES, config.INA_VBUS_CT_US, config.INA_VSH_CT_US)
                self.ina_batt.calibrate_for_max_current(max_current_a)
                self.has_ina_batt = True
            except Exception as e:
                print("WARN: INA226 batt init failed.", e)
                self.has_ina_batt = False
        else:
            print("WARN: INA226 batt not found at 0x{:02X}.".format(config.INA226_ADDR_BATT))
            self.has_ina_batt = False

        if config.INA226_ADDR_SYS in addrs:
            try:
                self.ina_sys = INA226(self.i2c, config.INA226_ADDR_SYS, config.SHUNT_RESISTANCE_OHMS)
                self.ina_sys.reset()
                self.ina_sys.configure_precision(config.INA_AVG_SAMPLES, config.INA_VBUS_CT_US, config.INA_VSH_CT_US)
                self.ina_sys.calibrate_for_max_current(max_current_a)
                self.has_ina_sys = True
            except Exception as e:
                print("WARN: INA226 sys init failed.", e)
                self.has_ina_sys = False
        else:
            print("WARN: INA226 sys not found at 0x{:02X}.".format(config.INA226_ADDR_SYS))
            self.has_ina_sys = False

    # -------------------------
    # BQ25895 (optional)
    # -------------------------
    def init_bq25895(self):
        addrs = self._scan()
        if config.BQ25895_ADDR in addrs:
            try:
                self.bq = BQ25895(self.i2c, config.BQ25895_ADDR)
                self.bq.set_charge_enable_i2c(False)
                self.bq.set_hiz(False)
                self.has_bq = True
            except Exception as e:
                print("WARN: BQ25895 init failed.", e)
                self.has_bq = False
        else:
            print("WARN: BQ25895 not found at 0x{:02X}.".format(config.BQ25895_ADDR))
            self.has_bq = False

    def init_all(self, max_current_a=5.0):
        self.init_i2c()
        self.init_expander()
        self.init_ina226(max_current_a=max_current_a)
        self.init_bq25895()

    # -------------------------
    # Inputs unified API
    # -------------------------
    def poll_button_edges(self):
        ev = {"menu": False, "left": False, "right": False, "ok": False}
        edges = self.inputs.poll_edges()
        for name, pressed in edges:
            if not pressed:
                continue
            if name == "MENU":
                ev["menu"] = True
            elif name == "LEFT":
                ev["left"] = True
            elif name == "RIGHT":
                ev["right"] = True
            elif name == "OK":
                ev["ok"] = True

        return ev

    # -------------------------
    # Charger enable helper
    # -------------------------
    def set_ce_enabled(self, enabled: bool):
        """
        Control /CE (active-low) if expander exists.
        No-op when expander is absent.
        """
        if self.exp is None:
            return
        self._set_pin(config.P_CE, 0 if enabled else 1)

    # -------------------------
    # Backwards-compatibility helpers (older UI harness)
    # -------------------------
    def read_inputs(self):
        if self.exp is None:
            self.in0, self.in1 = 0xFF, 0xFF
            return self.in0, self.in1
        self.in0, self.in1 = self.exp.read_all()
        return self.in0, self.in1

    def read_changes(self):
        if self.exp is None:
            return 0, 0, 0xFF, 0xFF
        chg0, chg1, new0, new1 = self.exp.read_changes()
        self.in0, self.in1 = new0, new1
        return chg0, chg1, new0, new1

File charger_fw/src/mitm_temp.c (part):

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// BEFORE app_run(), or spawn it as a FreeRTOS task.
//
// Wiring: AHT20+BMP280 board soldered in parallel with the OLED
//   SDA → GPIO5, SCL → GPIO6 (same bus, no config changes needed)
//   AHT20: 0x38, BMP280: 0x76
//
// External NTC: 10k pull-up to 3V3, NTC to GND, ADC channel 1 (GPIO1)
// =============================================================================

#include "mitm_temp.h"
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
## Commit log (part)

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2026-02-03 added hardware
2026-02-23 nearing production stage
2026-03-02 calibrated NTC, added server (to be tested)
2026-03-04 fixed cpu hog
2026-03-11 server + devices working over wifi
2026-03-11 working
2026-03-11 working-ish
2026-03-11 create docker setup
2026-03-11 allow access to host network

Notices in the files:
firmware/main.py:
self.oled.text("bSafe V1 (C)2026", 0, 0, 1)
